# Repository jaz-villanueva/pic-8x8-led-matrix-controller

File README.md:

# PIC Ping Pong Game (8x8 LED Matrix)

## Overview
This project implements a two-player ping pong game using a PIC16F877A microcontroller and an 8x8 LED matrix driven by the MAX7219. The system displays the ball and paddles on the matrix, with button inputs controlling paddle movement.

The focus of this implementation is the **physical hardware realization**, including PCB assembly, soldering, and validation of a working embedded system.

---

## My Contribution
- Performed full hardware assembly and soldering of the PCB implementation
- Translated schematic and design into a working physical circuit
- Verified system operation through testing and debugging
- Ensured reliable hardware integration with the firmware and LED matrix display

---

## Inspiration
This project was inspired by the original implementation:
https://github.com/icelal-kskn/PicPong

The system design and firmware concept were adapted from this repository and used as a reference for building the hardware implementation.

---

## Features
- Two-player ping pong gameplay
- 8x8 LED matrix display output
- MAX7219-driven multiplexing
- Button-controlled paddle movement
- Real-time ball movement and collision detection

---

## Hardware Used
- PIC16F877A Microcontroller
- MAX7219 LED Driver
- 8x8 LED Matrix Display
- Push Buttons (Player Controls)
- Resistors and Capacitors
- Crystal Oscillator
- 5V Power Supply

---

## Software Used
- MikroC PRO for PIC (Firmware Development)
- Proteus (Simulation)
- KiCad (PCB Design)

---

## Hardware Implementation
This project emphasizes the **physical construction of the system**, including:
- PCB assembly and soldering
- Component placement and wiring
- Ensuring clean and reliable solder joints
- Validating circuit behavior with firmware

---

## Build Output
(Add your images here)

---

## Documentation
📄 [Project Report](docs/pic-ping-pong-game-report.pdf)

---

## Attribution
This project is based on the following open-source implementation:
https://github.com/icelal-kskn/PicPong

The original work is licensed under the MIT License. This repository uses that work in accordance with its license.

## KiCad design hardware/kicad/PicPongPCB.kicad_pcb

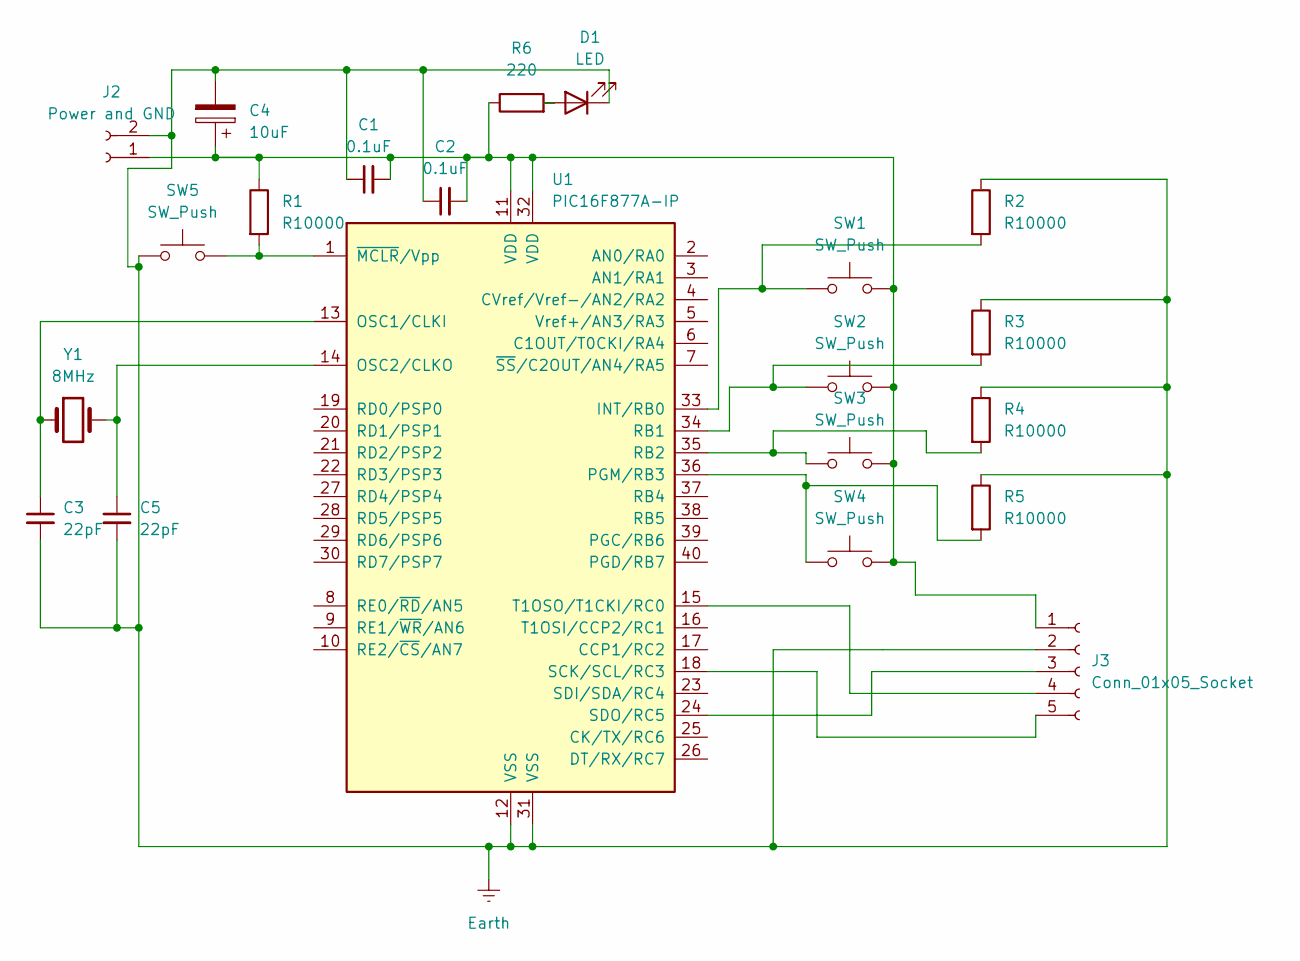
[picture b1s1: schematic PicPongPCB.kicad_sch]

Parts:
C1, C2: 0.1uF; C_Disc_D5.0mm_W2.5mm_P2.50mm
C3, C5: 22pF; C_Disc_D5.0mm_W2.5mm_P2.50mm
C4: 10uF; CP_Radial_D4.0mm_P2.00mm
D1: LED; LED_D3.0mm
J2: Power and GND; TerminalBlock_bornier-2_P5.08mm
J3: Conn_01x05_Socket; PinSocket_1x05_P2.54mm_Vertical
R1, R2, R3, R4, R5: R10000; R_Axial_DIN0207_L6.3mm_D2.5mm_P7.62mm_Horizontal
R6: 220; R_Axial_DIN0207_L6.3mm_D2.5mm_P7.62mm_Horizontal
SW1, SW2, SW3, SW4, SW5: SW_Push; SW_PUSH_6mm_H5mm
U1: PIC16F877A-IP; DIP-40_W15.24mm
Y1: 8MHz; Crystal_HC49-U_Vertical

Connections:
Earth: C1.1, C2.1, C3.2, C4.2, C5.2, D1.1 (K), J2.2, J3.2, R2.1, R3.1, R4.1, R5.1, SW5.1, U1.12 (VSS), U1.31 (VSS)
unnamed: D1.2 (A), R6.2
unnamed: C1.2, C2.2, C4.1, J2.1, J3.1, R1.1, R6.1, SW1.2, SW2.2, SW3.2, SW4.2, U1.11 (VDD), U1.32 (VDD)
unnamed: J3.3, U1.24 (SDO/RC5)
unnamed: J3.4, U1.15 (T1OSO/T1CKI/RC0)
unnamed: J3.5, U1.18 (SCK/SCL/RC3)
unnamed: R2.2, SW1.1, U1.33 (INT/RB0)
unnamed: C3.1, U1.13 (OSC1/CLKI), Y1.1
unnamed: C5.1, U1.14 (OSC2/CLKO), Y1.2
unnamed: R5.2, SW4.1, U1.36 (PGM/RB3)
unnamed: R3.2, SW2.1, U1.34 (RB1)
unnamed: R4.2, SW3.1, U1.35 (RB2)
unnamed: R1.2, SW5.2, U1.1 (~MCLR/Vpp)

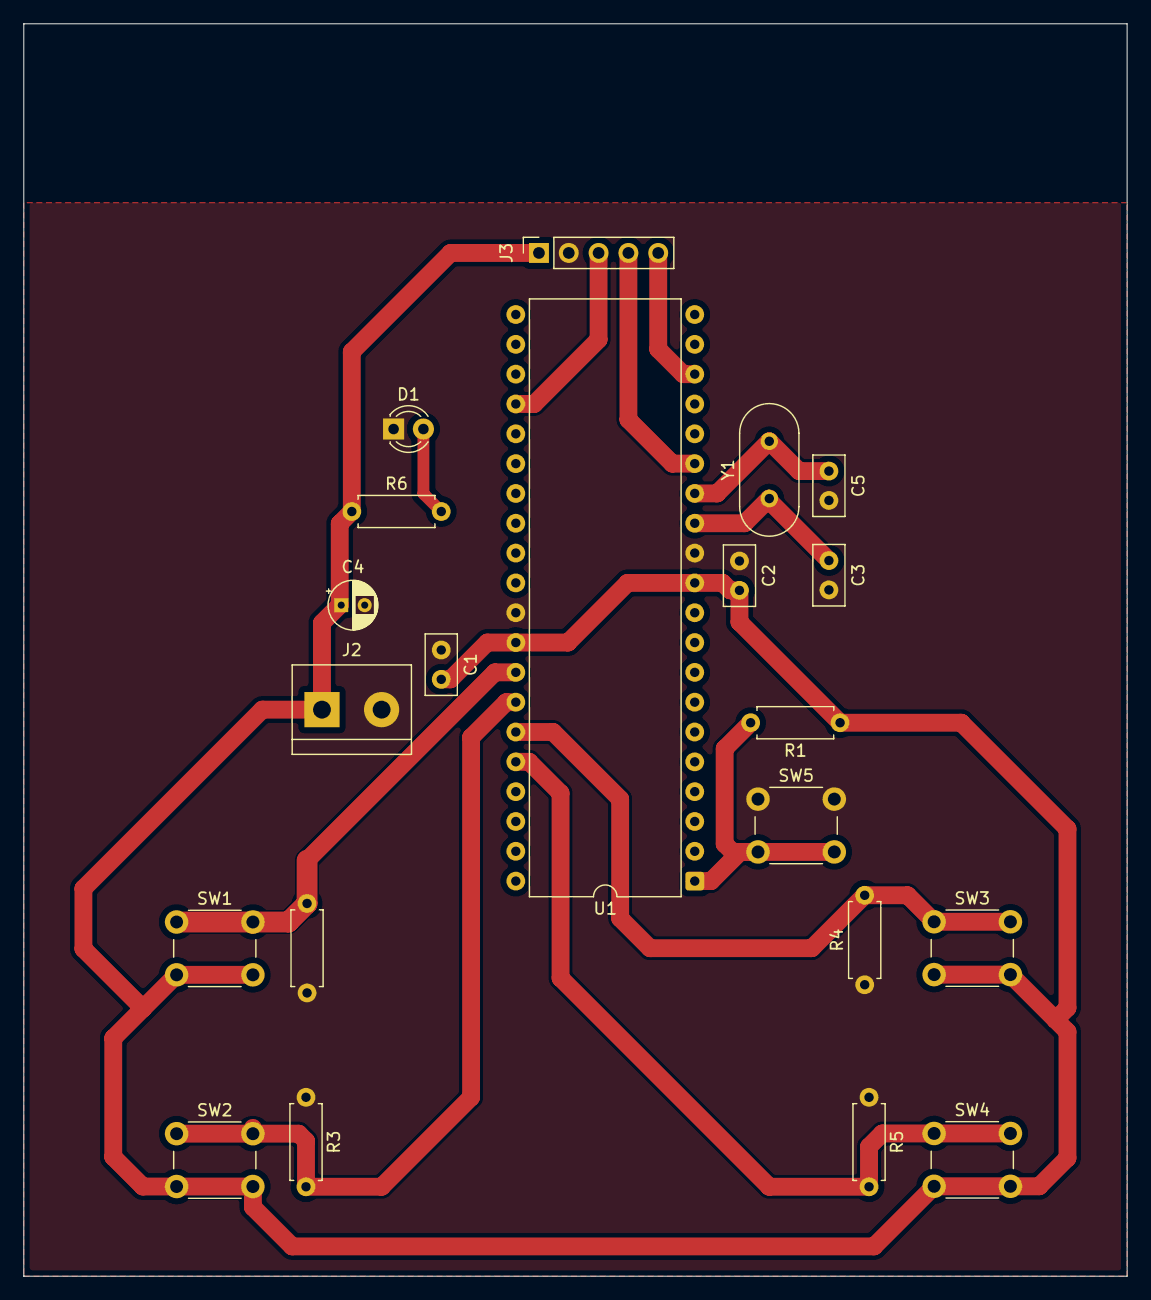
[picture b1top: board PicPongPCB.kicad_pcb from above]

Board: 2 copper layers, 94.0 x 106.7 mm, 21 parts (0 on the bottom side), 13 nets.

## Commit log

2026-04-19 Create datasheets
2026-04-19 Create one
2026-04-19 Create pcb
2026-04-19 Create sim
2026-04-19 Create pic1
2026-04-19 Create LICENSE
